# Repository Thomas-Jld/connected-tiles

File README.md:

# Connected tiles

## Description

A set of square tiles that can be assembled to form a connected grid. The tiles can be used to create a board game to play tic-tac-toe, checkers, chess, or any other game that can be played on a square grid. A motherboard gathers information from the tiles and sends it to a computer via USB.

## Tiles

### Requirements

A tile must be able to:
- Connect to other tiles using a magnetic connection
- Know which tiles are connected to them and where the connected tile is located (**4 pins, 1 per direction**).
- Communicate with the motherboard via I2C (**8 pins, 2 per direction**).
- Receive power from the motherboard and power the connected tiles (**8 pins, 2 per direction**).
- Display an animation or a status color using Neopixels.
- Detect which piece is on top of it using a hall effect sensor.

### Piece detection

Sensing what piece was placed on top of the tile can be done in multiple ways:

**Currently used**

- 1D Hall effect sensor
- Color sensor
- Capacitive sensor

**Potential implementations**
- RFID
- 3D Hall effect sensor
- LC Resonance
- Weight sensor

### Components

**MCU**
- ATMEGA328PB-MU-ND [(1)](https://www.digikey.com/en/products/detail/microchip-technology/ATMEGA328PB-MU/5638814) [(2)](https://ww1.microchip.com/downloads/en/DeviceDoc/ATmega48A-PA-88A-PA-168A-PA-328-P-DS-DS40002061B.pdf)

Others:
- ATMEGA328P-AN [(1)](https://www.digikey.com/en/products/detail/microchip-technology/ATMEGA328P-AN/2357082)
- ATMEGA328-AU [(1)](https://www.digikey.com/en/products/detail/ATMEGA328-AU/ATMEGA328-AU-ND/2271029)

**Crystal**
- 16MHz 2151-RH100-16.000-9-1018-EXT-TRCT-ND [(1)](https://www.digikey.com/en/products/detail/raltron-electronics/RH100-16-000-9-1018-EXT-TR/13150831)

Others:

- 20MHz RH100-20.000-16-3030-TR [(1)](https://www.digikey.com/en/products/detail/ilsi/HC49USM-FF3F18-20-000MHZ/12619607)
- 20MHz 830108207209 CFPX-180 [(1)](https://www.digikey.com/en/products/detail/w%C3%BCrth-elektronik/830108207209/13900466)
- 20MHz HC49USM-FF3F18 [(1)](https://www.digikey.com/en/products/detail/ilsi/HC49USM-FF3F18-20-000MHZ/12619607)

**Neopixels**
- SK6812 [(1)](https://cdn-shop.adafruit.com/product-files/1138/SK6812+LED+datasheet+.pdf)

Others:

- WS2812B [(1)](https://cdn-shop.adafruit.com/datasheets/WS2812B.pdf)

**Hall effect sensor**
- DRV5053EA [(1)](https://www.digikey.com/en/products/detail/texas-instruments/DRV5053EAQDBZR/5015735)

Others:

- A1301 [(1)](https://media.digikey.com/pdf/Data%20Sheets/Allegro%20PDFs/A1301,02.pdf)
- DRV5056ZAQDBZR [(1)](https://www.mouser.fr/ProductDetail/Texas-Instruments/DRV5056Z4QDBZR?qs=sGAEpiMZZMu5vlrqIFXt5bBKj94x8jjB1VhsLdgRjqTXdlweh5XYMA%3D%3D)

**Connection pins**
- U Shape Pin headers [(1)](https://www.aliexpress.us/item/2251832806357191.html) [(2)](https://fr.aliexpress.com/i/32992671943.html) [(3)](https://www.digikey.com/en/products/detail/aries-electronics/16-675-191/4208672) [(4)](https://www.wayconn.com/ph254-1u26/)
- 3mm header [(1)](https://www.aliexpress.us/item/2251832663748459.html)

Others:

- Pogo pins [(1)](https://www.digikey.com/en/products/detail/mill-max-manufacturing-corp/829-22-020-20-002101/4007088) [(2)](https://www.mouser.com/ProductDetail/Mill-Max/854-22-003-20-001101?qs=XFe3dyCRgQjPe3AesOqKJA%3D%3D) [(3)](https://fr.aliexpress.com/item/1005003579709688.html) [(4)](https://www.digikey.com/en/products/detail/mill-max-manufacturing-corp/829-22-003-20-001101/2416224) [(5)](https://www.aliexpress.us/item/2255800744344835.html)

**Mating targets**
Magnet strength and Gauss calculator [here](https://www.kjmagnetics.com/calculator.asp)

- 399-10-164-10-008000 [(1)](https://www.digikey.com/en/products/detail/mill-max-manufacturing-corp/399-10-106-10-008000/4456257)

**Magnets**
- 8195 (6.35mm x 1.59mm) [(1)](https://www.digikey.com/en/products/detail/radial-magnets-inc/8195/555329)
- *Piece alignment (Cylinder: 1/8" by 1/32")* [(1)](https://www.kjmagnetics.com/proddetail.asp?prod=D201)
- *Edge connection (Block: 1/16" by 1/16" by 1/8")* [(1)](https://www.kjmagnetics.com/proddetail.asp?prod=B112)

Others:

- 5mm x 1mm neodymium magnets [(1)](https://www.magnetiques.fr/magnetique,aimant-rond-plat-552-fr.html)

**Reset tactile switch**
- PTS526 SM15 SMTR2 LFS CKN12220-1-ND [(1)](https://www.digikey.com/en/products/detail/c-k/PTS526-SM15-SMTR2-LFS/10056625)

Others:

- TS04-66-43-BK-100-SMT [(1)](https://www.digikey.com/en/products/detail/cui-devices/TS04-66-43-BK-100-SMT/15634299)

**Capacitors**
- *Crystal:* 22pf 0603 0603N220J500CT [(1)](https://www.digikey.com/en/products/detail/walsin-technology-corporation/0603N220J500CT/9355000)
- *Hall effect sensor:* 12pf 0603 0603N120J500CT [(1)](https://www.digikey.com/en/products/detail/walsin-technology-corporation/0603N120J500CT/9354977)
- *Capacitive Touch:* 22nf 0402 C0402C223K5REC7411 [(1)](https://www.digikey.com/en/products/detail/kemet/C0402C223K5REC7411/8645043)
- *AREF decoupler:* 100nf 0603 CL10B104KB8NNWC [(1)](https://www.digikey.com/en/products/detail/samsung-electro-mechanics/CL10B104KB8NNWC/3887593)

**LED**
- *Serial com* B1931UD-05D000314U1930 [(1)](https://www.digikey.com/en/products/detail/harvatek-corporation/B1931UD-05D000314U1930/15861266)
- *Color sensor (CS)* T2133BGR-20C0001U2U1930 [(1)](https://www.digikey.com/en/products/detail/harvatek-corporation/T2133BGR-20C0001U2U1930/17830297)

**Phototransistor**
- *Color sensor* B19H1PT--H9C000214U1930 [(1)](https://www.digikey.com/en/products/detail/harvatek-corporation/B19H1PT-H9C000214U1930/13574171)

**Resistors**
- *Neopixels:* 300 Ohm 0603 RC0603JR-07300RL [(1)](https://www.digikey.com/en/products/detail/yageo/RC0603JR-07300RL/726765)
- *Serial com led:* 300 Ohm 0603 RC0603JR-07300RL [(1)](https://www.digikey.com/en/products/detail/yageo/RC0603JR-07300RL/726765)
- *MCU Pull-up reset resistor:* 10k Ohm 0603 RC0603JR-0710KL [(1)](https://www.digikey.com/en/products/detail/yageo/RC0603JR-0710KL/726700)
- *Color sensor:* 10k Ohm 0603 RC0603JR-0710KL [(1)](https://www.digikey.com/en/products/detail/yageo/RC0603JR-0710KL/726700)
- *R channel of the CS RGB led:* 150 Ohm 0603 RC0603JR-07150RL [(1)](https://www.digikey.com/en/products/detail/yageo/RC0603JR-07150RL/726714)
- *G channel of the CS RGB led:* 90 Ohm 0603 RC0603JR-0791RL [(1)](https://www.digikey.com/en/products/detail/yageo/RC0603JR-0791RL/726840)
- *B channel of the CS RGB led:* 90 Ohm 0603 RC0603JR-0791RL [(1)](https://www.digikey.com/en/products/detail/yageo/RC0603JR-0791RL/726840)
- *Capacitive touch:* 1k Ohm 0603 RC0603JR-071KL [(1)](https://www.digikey.com/en/products/detail/yageo/RC0603JR-071KL/726677)

### Tile detection mechanism

When the tiles are powered up, their "connection" pins are set as Outputs and are set to HIGH...

### Pieces

A piece category is defined by the magnetic field it generates. For example, in chess, the pieces are:
- Pawn: 1 magnet
- Rook: 2 magnets
- Knight: 3 magnets
- Bishop: 4 magnets
- Queen: 5 magnets
- King: 6 magnets

## Motherboard

### Requirements

The motherboard should be able to:
- Power up to 64 tiles, each tile consuming up to 250mA (16A total).
- Communicate with each tile using I2C:
  The added capacitance of each tile could be a problem (regular I2C is limited to 400pF), which means that the bus will either need to be slowed down or an extender will be placed on the motherboard (the [LTC4311](https://www.adafruit.com/product/4756) allows the bus coupling capacitance to be up to 4000pF)
- Communicate with the computer using USB or operate autonomously.

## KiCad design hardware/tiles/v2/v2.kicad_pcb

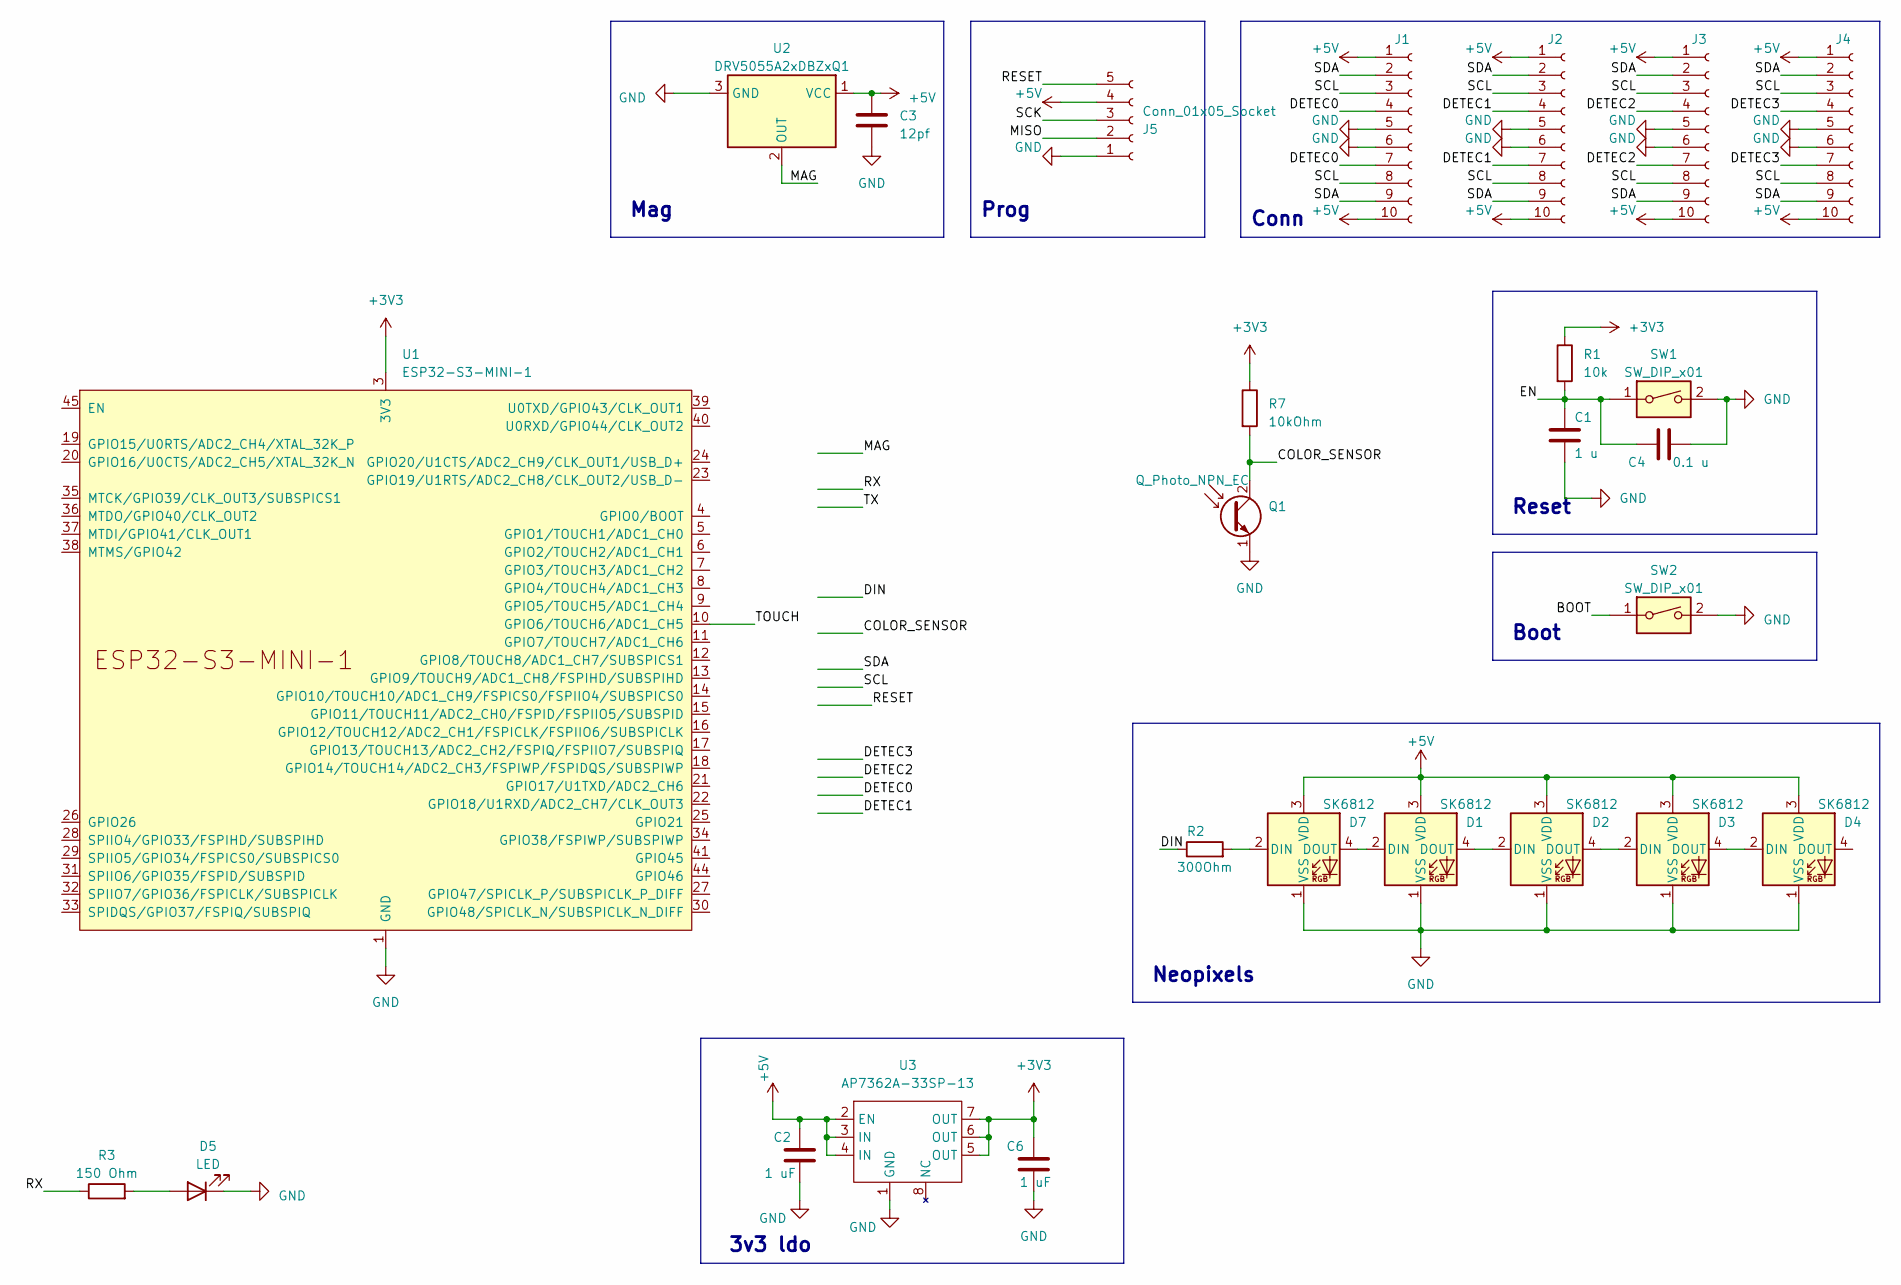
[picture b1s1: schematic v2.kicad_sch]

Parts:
C1: 1 u; C_0603_1608Metric
C2, C6: 1 uF; C_0603_1608Metric_Pad1.08x0.95mm_HandSolder
C3: 12pf; C_0603_1608Metric_Pad1.08x0.95mm_HandSolder
C4: 0.1 u; C_0603_1608Metric
D1, D2, D3, D4, D7: SK6812; LED_SK6812_PLCC4_5.0x5.0mm_P3.2mm
D5: LED; LED_0603_1608Metric_Pad1.05x0.95mm_HandSolder
J1, J2, J3, J4: Conn_01x10_Socket; PinSocket_1x10_P2.54mm_Vertical
J5: Conn_01x05_Socket; PinSocket_1x05_P2.54mm_Vertical
Q1: Q_Photo_NPN_EC; R_0603_1608Metric_Pad0.98x0.95mm_HandSolder
R1: 10k; R_0603_1608Metric
R2: 300Ohm; R_0603_1608Metric_Pad0.98x0.95mm_HandSolder
R3: 150 Ohm; R_0603_1608Metric_Pad0.98x0.95mm_HandSolder
R7: 10kOhm; R_0603_1608Metric_Pad0.98x0.95mm_HandSolder
SW1, SW2: SW_DIP_x01; SW_Push_1P1T_XKB_TS-1187A
U1: ESP32-S3-MINI-1; ESP32-S3-MINI-1U
U2: DRV5055A2xDBZxQ1; SOT-23
U3: AP7362A-33SP-13; SOIC127P600X163-9N

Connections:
+3V3: C6.1, R1.1, R7.1, U1.3 (3V3), U3.5 (OUT), U3.6 (OUT), U3.7 (OUT); also elsewhere on the board
+5V: C2.1, C3.1, D1.3 (VDD), D2.3 (VDD), D3.3 (VDD), D4.3 (VDD), D7.3 (VDD), J1.1, J1.10, J2.1, J2.10, J3.1, J3.10, J4.1, J4.10, J5.4, U2.1 (VCC), U3.2 (EN), U3.3 (IN), U3.4 (IN)
/BOOT: SW2.1
/COLOR_SENSOR: Q1.2 (C), R7.2; also elsewhere on the board
/DETEC0: J1.4, J1.7
/DETEC1: J2.4, J2.7
/DETEC2: J3.4, J3.7
/DETEC3: J4.4, J4.7
/DIN: R2.1
/EN: C1.1, C4.1, R1.2, SW1.1
/MAG: U2.2 (OUT)
/MISO: J5.2
/RESET: J5.5
/RX: R3.1
/SCK: J5.3
/SCL: J1.3, J1.8, J2.3, J2.8, J3.3, J3.8, J4.3, J4.8
/SDA: J1.2, J1.9, J2.2, J2.9, J3.2, J3.9, J4.2, J4.9
/TOUCH: U1.10 (GPIO6/TOUCH6/ADC1_CH5)
GND: C1.2, C2.2, C3.2, C4.2, C6.2, D1.1 (VSS), D2.1 (VSS), D3.1 (VSS), D4.1 (VSS), D5.1 (K), D7.1 (VSS), J1.5, J1.6, J2.5, J2.6, J3.5, J3.6, J4.5, J4.6, J5.1, Q1.1 (E), SW1.2, SW2.2, U1.1 (GND), U1.2 (GND), U1.42 (GND), U1.43 (GND), U1.46 (GND), U1.47 (GND), U1.48 (GND), U1.49 (GND), U1.50 (GND), U1.51 (GND), U1.52 (GND), U1.53 (GND), U1.54 (GND), U1.55 (GND), U1.56 (GND), U1.57 (GND), U1.58 (GND), U1.59 (GND), U1.60 (GND), U1.61 (GND), U1.62 (GND), U1.63 (GND), U1.64 (GND), U1.65 (GND), U2.3 (GND), U3.1 (GND)
unnamed: D1.2 (DIN), D7.4 (DOUT)
unnamed: D1.4 (DOUT), D2.2 (DIN)
unnamed: D2.4 (DOUT), D3.2 (DIN)
unnamed: D3.4 (DOUT), D4.2 (DIN)
unnamed: D5.2 (A), R3.2
unnamed: D7.2 (DIN), R2.2

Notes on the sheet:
Conn
Mag
Neopixels
3v3 ldo
Prog
Boot
Reset

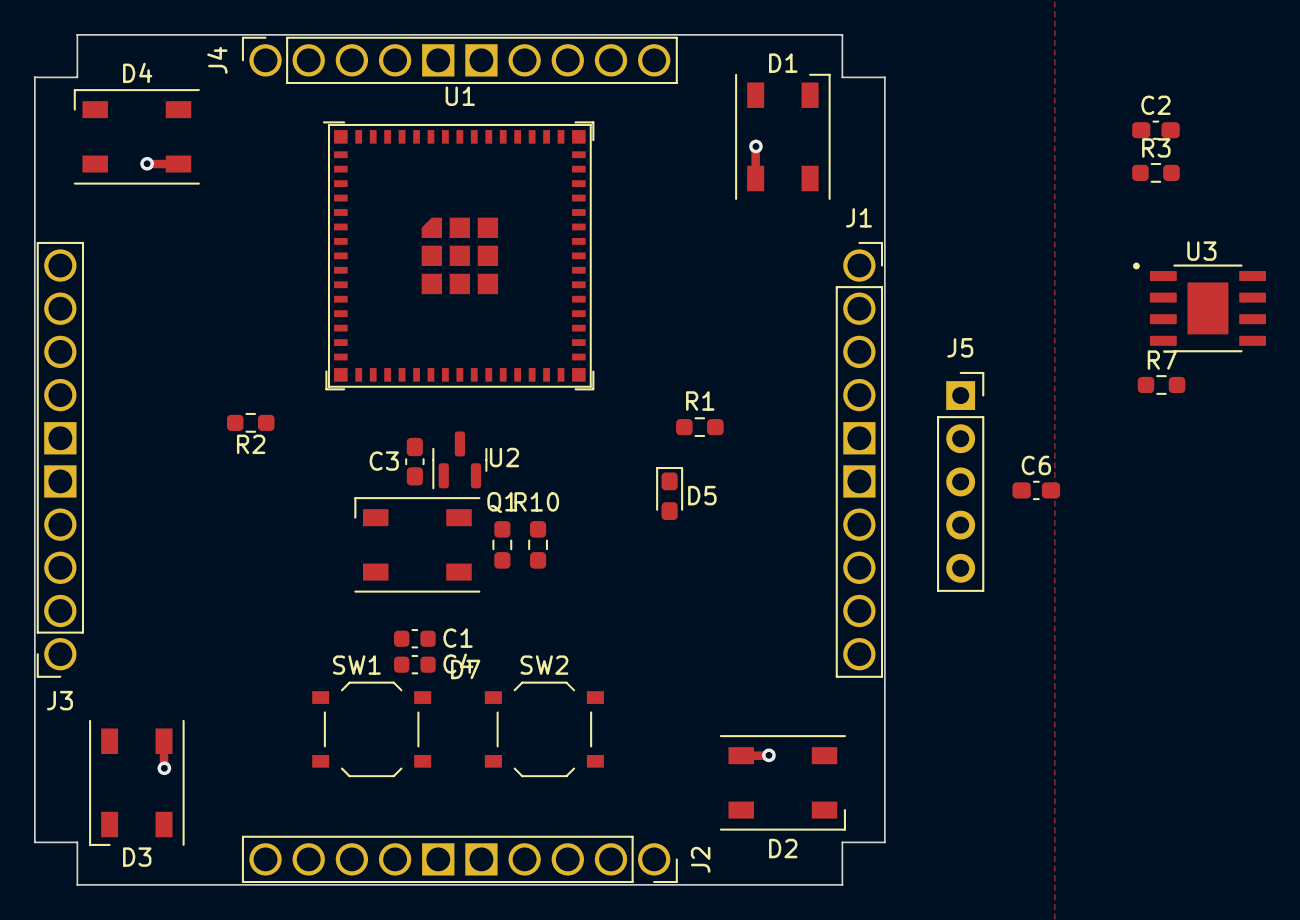
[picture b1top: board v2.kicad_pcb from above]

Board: 4 copper layers, 50.0 x 50.0 mm, 27 parts (0 on the bottom side), 17 nets.

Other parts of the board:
R10: 10kOhm; R_0603_1608Metric_Pad0.98x0.95mm_HandSolder

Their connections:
+3V3: R10.1; also elsewhere on the board
/COLOR_SENSOR: R10.2; also elsewhere on the board

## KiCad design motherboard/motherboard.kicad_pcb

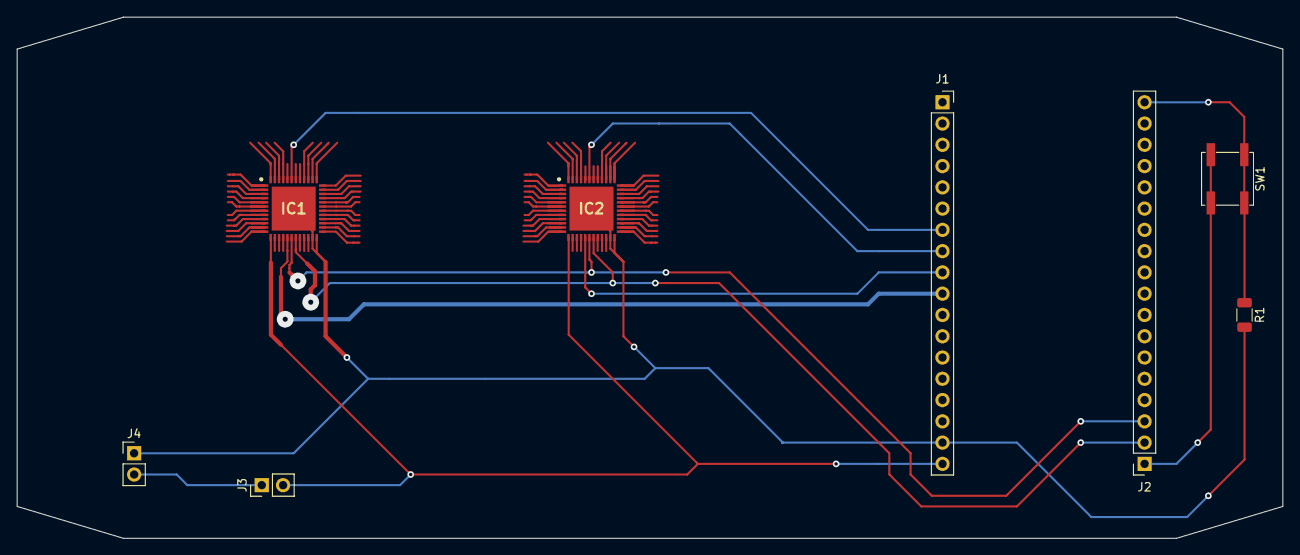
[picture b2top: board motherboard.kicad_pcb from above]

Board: 2 copper layers, 151.1 x 62.2 mm, 8 parts (0 on the bottom side), 11 nets.

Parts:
IC1, IC2: ADG731BCPZ; QFN50P700X700X100-49N-D
J1, J2: Conn_01x18_Female; PinSocket_1x18_P2.54mm_Vertical
J3, J4: Conn_01x02_Female; PinHeader_1x02_P2.54mm_Vertical
R1: R; R_1206_3216Metric
SW1: SW_Push; SW_SPST_EVPBF

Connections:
+5V: IC1.13, IC2.13, J1.18, J3.2
DATA1: IC1.43, J1.7
DATA2: IC2.43, J1.8
DIN: IC1.18, IC2.18, J2.3
GNDREF: IC1.23, IC1.24, IC1.49, IC2.23, IC2.24, IC2.49, J1.17, J4.1, R1.2
unnamed: J2.1, SW1.2
unnamed: J2.18, R1.1, SW1.1
unnamed: J3.1, J4.2
SCLK: IC1.19, IC2.19, J2.2
SYNC1: IC1.17, J1.10
SYNC2: IC2.17, J1.9

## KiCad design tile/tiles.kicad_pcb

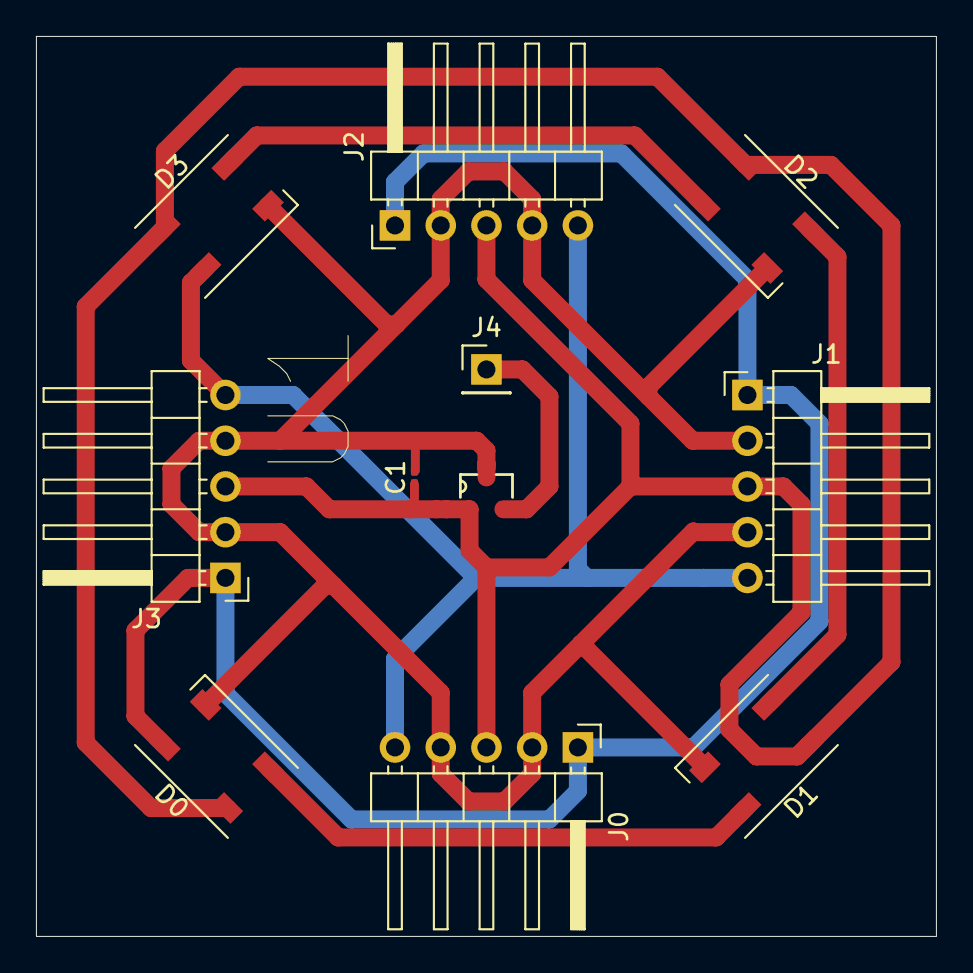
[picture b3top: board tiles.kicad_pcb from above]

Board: 2 copper layers, 50.0 x 50.0 mm, 11 parts (0 on the bottom side), 8 nets.

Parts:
C1: 0.01µf; C_0201_0603Metric
D0, D1, D2, D3: SK6812; LED_SK6812_PLCC4_5.0x5.0mm_P3.2mm
J0, J1, J2, J3: Conn_01x05; PinHeader_1x05_P2.54mm_Horizontal
J4: Conn_01x01_Female; PinHeader_1x01_P2.54mm_Vertical
U1: A1302KUA-T; SOT95P290X110-3N

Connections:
/DIN: D0.2, J0.1, J1.1, J2.1, J3.1
/DOUT: D3.4, J0.5, J1.5, J2.5, J3.5
/GND: C1.2, D0.1, D1.1, D2.1, D3.1, J0.2, J0.4, J1.2, J1.4, J2.2, J2.4, J3.2, J3.4, U1.3
/VCC: C1.1, D0.3, D1.3, D2.3, D3.3, J0.3, J1.3, J2.3, J3.3, U1.1
unnamed: D0.4, D1.2
unnamed: D1.4, D2.2
unnamed: D2.4, D3.2
unnamed: J4.1, U1.2

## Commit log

2021-06-14 Adding tiles
2021-06-14 Adding Kicad project files
2021-06-14 added gitignore
2021-06-14 moved project
2021-06-20 add app
2021-06-21 Neopixel tests and loops
2023-05-08 Pcb hardware update
2023-05-09 Adding cover image
2023-05-09 Updating readme
2023-05-11 Updating PCB with Capacitive touch and Color sensor
2023-05-17 Last atmega238 update
2023-05-19 Updating pcb to support U-shaped pin connection, adding AREF decoupler
2025-01-24 Quick save
